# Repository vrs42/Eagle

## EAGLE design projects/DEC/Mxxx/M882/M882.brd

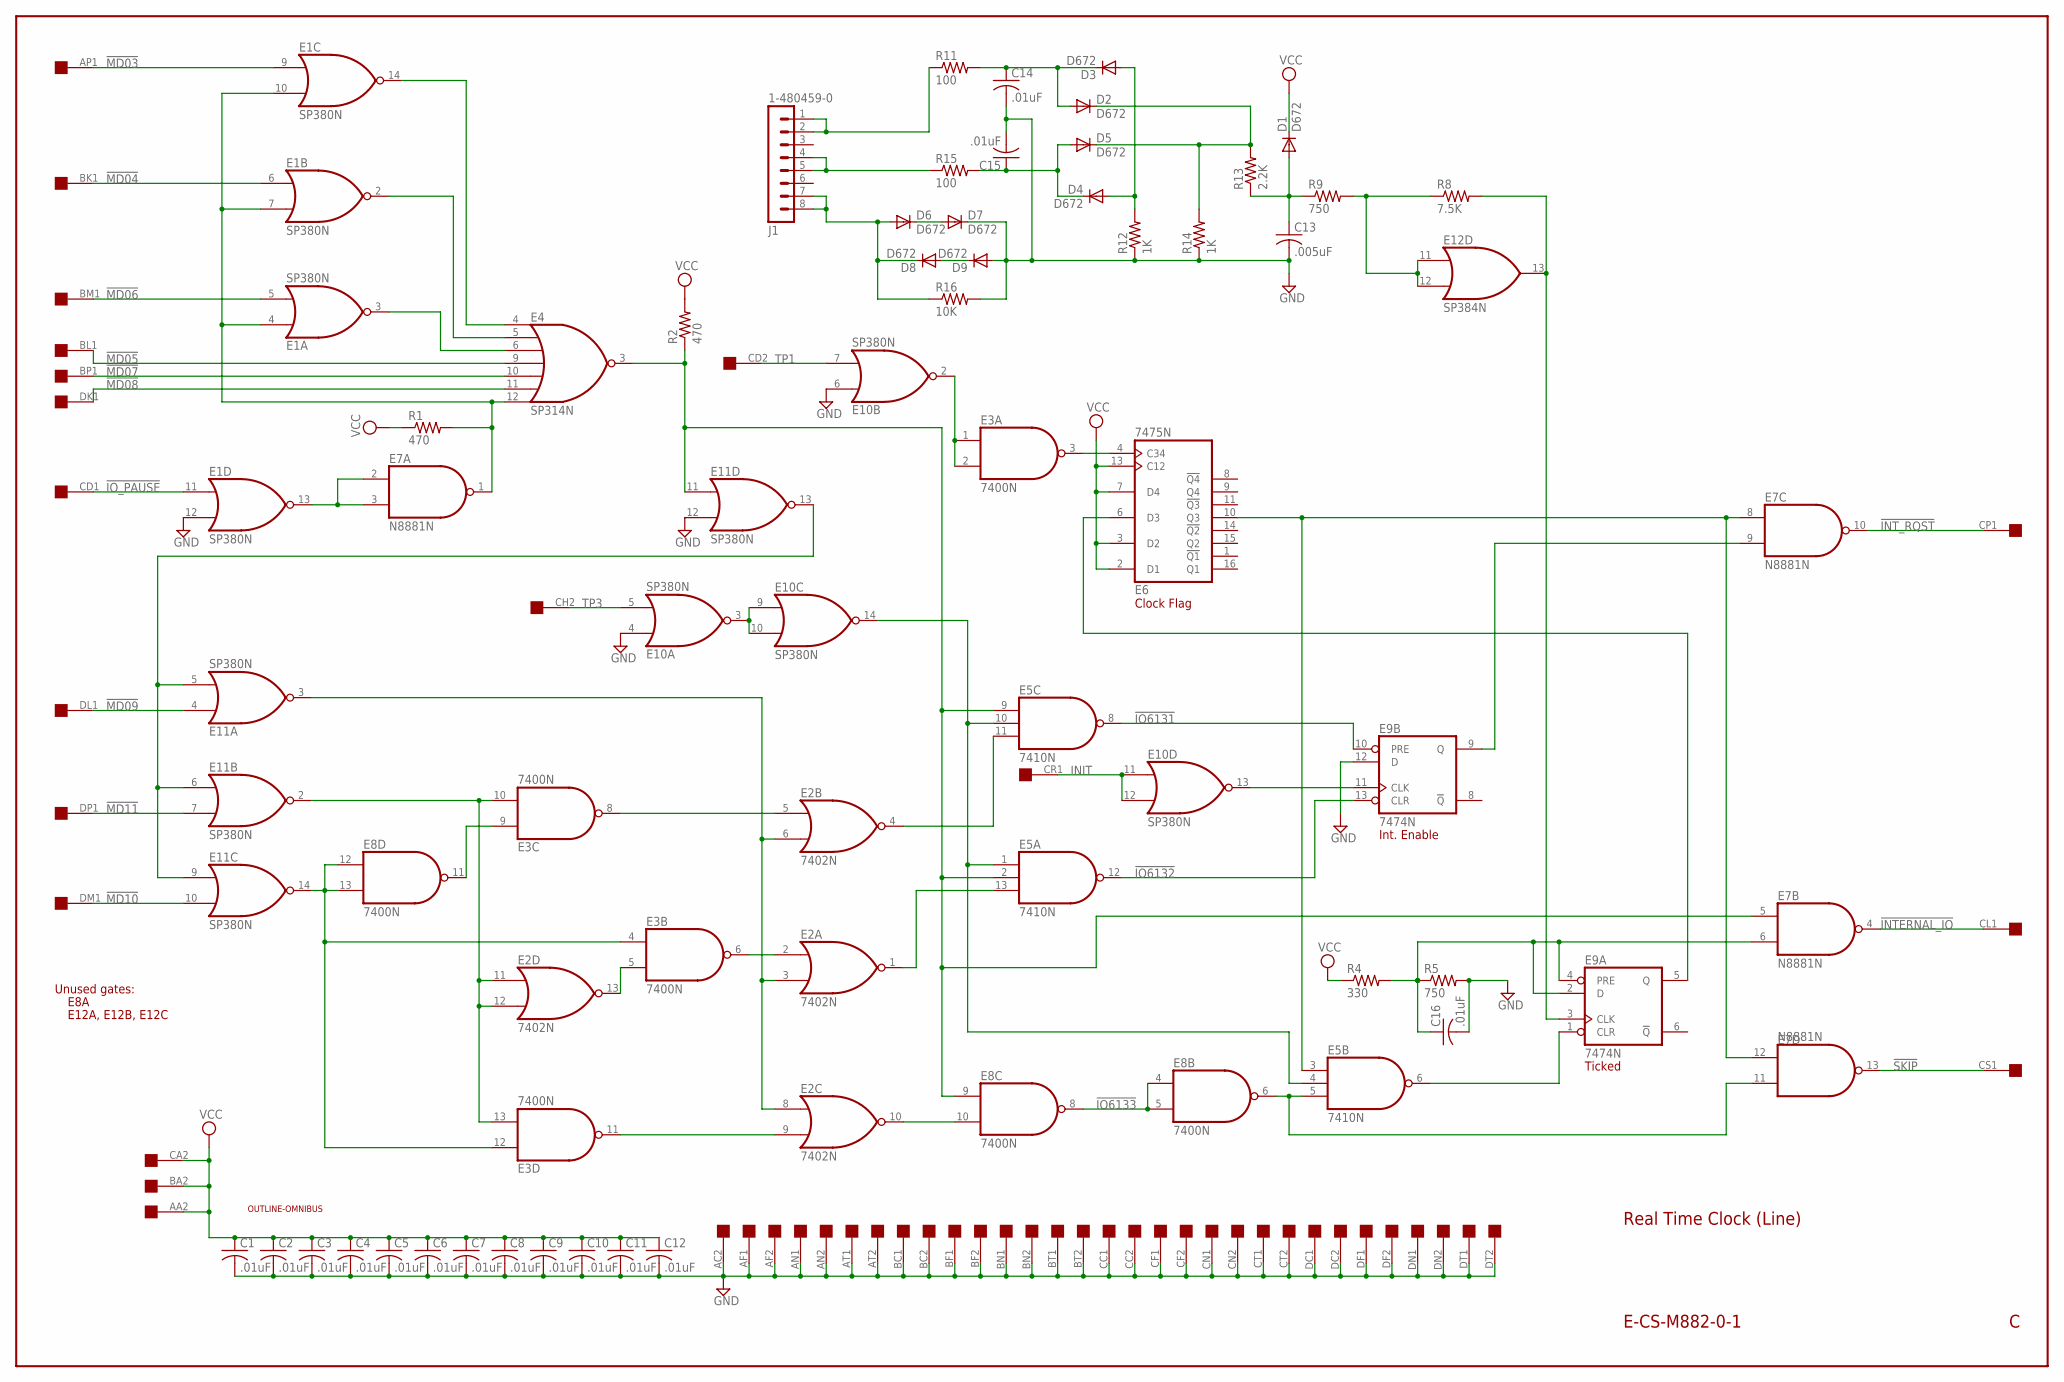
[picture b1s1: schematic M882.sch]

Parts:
C1, C2, C3, C4, C5, C6, C7, C8, C9, C10, C11, C12, C14, C15, C16: .01uF; C050-025X075
C13: .005uF; C050-025X075
D1, D2, D3, D4, D5, D6, D7, D8, D9: D672; DO35-10
E1, E10, E11: SP380N; DIL14
E2: 7402N; DIL14
E3, E8: 7400N; DIL14
E4: SP314N; DIL14
E5: 7410N; DIL14
E6: 7475N; DIL16
E7: N8881N; DIL14
E9: 7474N; DIL14
E12: SP384N; DIL14
EDGE: QUAD; EDGE-CON8
J1: 1-480459-0
R1, R2: 470; 0207/10
R4: 330; 0207/10
R5, R9: 750; 0207/10
R8: 7.5K; 0207/10
R11, R15: 100; 0207/10
R12, R14: 1K; 0207/10
R13: 2.2K; 0207/10
R16: 10K; 0207/10
U$1: OUTLINE-OMNIBUS; OMNIBUS

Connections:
!BIOPAUSE: E1.4 (I0), E1.7 (I1), E1.10 (I1), E4.12 (I6), E7.1 (O), R1.2
!DO_CLSK: E5.6 (O), E9.1 (CLR)
!INIT: E9.11 (CLK), E10.13 (O)
!INTERNAL_IO: E7.4 (O), EDGE.CL1
!INT_RQST: E7.10 (O), EDGE.CP1
!IO6131: E5.8 (O), E9.10 (PRE)
!IO6132: E5.12 (O), E9.13 (CLR)
!IO6133: E8.4 (I0), E8.5 (I1), E8.8 (O)
!IO_PAUSE: E1.11 (I0), EDGE.CD1
!MAYBECLDI: E2.2 (I0), E3.6 (O)
!MAYBE_CLEI: E2.5 (I0), E3.8 (O)
!MAYBE_CLSK: E2.9 (I1), E3.11 (O)
!MD03: E1.9 (I0), EDGE.AP1
!MD04: E1.6 (I0), EDGE.BK1
!MD05: E4.9 (I3), EDGE.BL1
!MD06: E1.5 (I1), EDGE.BM1
!MD07: E4.10 (I4), EDGE.BP1
!MD08: E4.11 (I5), EDGE.DK1
!MD09: E11.4 (I0), EDGE.DL1
!MD10: E11.10 (I1), EDGE.DM1
!MD11: E11.7 (I1), EDGE.DP1
!MYIOT: E11.5 (I1), E11.6 (I0), E11.9 (I0), E11.13 (O)
!MYMD10: E3.9 (I0), E8.11 (O)
!MYMD11: E2.13 (O), E3.5 (I1)
!SKIP: E7.13 (O), EDGE.CS1
!TP1: E3.1 (I0), E3.2 (I1), E10.2 (O)
!TP3: E10.3 (O), E10.9 (I0), E10.10 (I1)
+3V3: C16.1, E7.6 (I1), E9.2 (D), E9.4 (PRE), R4.2, R5.1
BOSCIN: E9.3 (CLK), E12.13 (O), R8.2
BTP1: E3.3 (O), E6.4 (C34)
BTP3: E5.1 (I0), E5.4 (I1), E5.10 (I1), E10.14 (O)
CK_FLAG: E5.3 (I0), E6.10 (Q3), E7.8 (I0), E7.12 (I1)
CLDI: E2.1 (O), E5.13 (I2)
CLIE: E2.4 (O), E5.11 (I2)
CLSK: E2.10 (O), E8.10 (I1)
GND: C1.2, C2.2, C3.2, C4.2, C5.2, C6.2, C7.2, C8.2, C9.2, C10.2, C11.2, C12.2, C13.2, C14.2, C15.2, C16.2, D7.C, D9.A, E1.1 (GND), E1.12 (I1), E2.7 (GND), E3.7 (GND), E4.1 (GND), E5.7 (GND), E6.12 (GND), E7.7 (GND), E8.7 (GND), E9.7 (GND), E9.12 (D), E10.1 (GND), E10.4 (I0), E10.6 (I0), E11.1 (GND), E11.12 (I1), E12.1 (GND), EDGE.AC2, EDGE.AF1, EDGE.AF2, EDGE.AN1, EDGE.AN2, EDGE.AT1, EDGE.AT2, EDGE.BC1, EDGE.BC2, EDGE.BF1, EDGE.BF2, EDGE.BN1, EDGE.BN2, EDGE.BT1, EDGE.BT2, EDGE.CC1, EDGE.CC2, EDGE.CF1, EDGE.CF2, EDGE.CN1, EDGE.CN2, EDGE.CT1, EDGE.CT2, EDGE.DC1, EDGE.DC2, EDGE.DF1, EDGE.DF2, EDGE.DN1, EDGE.DN2, EDGE.DT1, EDGE.DT2, R5.2, R12.1, R14.1, R16.2
INIT: E10.11 (I0), E10.12 (I1), EDGE.CR1
IO6133: E5.5 (I2), E7.11 (I0), E8.6 (O)
IOPMD03: E1.14 (O), E4.4 (I0)
IOPMD04: E1.2 (O), E4.5 (I1)
IOPMD06: E1.3 (O), E4.6 (I2)
IO_PAUSE: E1.13 (O), E7.2 (I0), E7.3 (I1)
IRQ_ENABLE: E7.9 (I1), E9.9 (Q)
MYIOT: E4.3 (O), E5.2 (I1), E5.9 (I0), E7.5 (I0), E8.9 (I0), E11.11 (I0), R2.1
MYMD09: E2.3 (I1), E2.6 (I1), E2.8 (I0), E11.3 (O)
MYMD10: E3.4 (I0), E3.12 (I0), E8.12 (I0), E8.13 (I1), E11.14 (O)
MYMD11: E2.11 (I0), E2.12 (I1), E3.10 (I1), E3.13 (I1), E11.2 (O)
unnamed: J1.1, J1.2, R11.1
unnamed: J1.4, J1.5, R15.1
unnamed: D6.A, D8.C, J1.7, J1.8, R16.1
unnamed: D6.C, D7.A
unnamed: D8.A, D9.C
unnamed: D2.C, D5.C, R13.2, R14.2
unnamed: C14.1, D2.A, D3.C, R11.2
unnamed: D3.A, D4.A, R12.2
unnamed: C13.1, D1.A, R9.1, R13.1
unnamed: C15.1, D4.C, D5.A, R15.2
OSCIN: E12.11 (I0), E12.12 (I1), R8.1, R9.2
TICKED: E6.6 (D3), E9.5 (Q)
TP1: E10.7 (I1), EDGE.CD2
TP3: E10.5 (I1), EDGE.CH2
VCC: C1.1, C2.1, C3.1, C4.1, C5.1, C6.1, C7.1, C8.1, C9.1, C10.1, C11.1, C12.1, D1.C, E1.8 (VCC), E2.14 (VCC), E3.14 (VCC), E4.8 (VCC), E5.14 (VCC), E6.2 (D1), E6.3 (D2), E6.5 (VCC), E6.7 (D4), E6.13 (C12), E7.14 (VCC), E8.14 (VCC), E9.14 (VCC), E10.8 (VCC), E11.8 (VCC), E12.8 (VCC), EDGE.AA2, EDGE.BA2, EDGE.CA2, R1.1, R2.2, R4.1

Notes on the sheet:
Unused gates:
E12A, E12B, E12C
E8A
E-CS-M882-0-1
Real Time Clock (Line)
Int. Enable
Ticked
Clock Flag

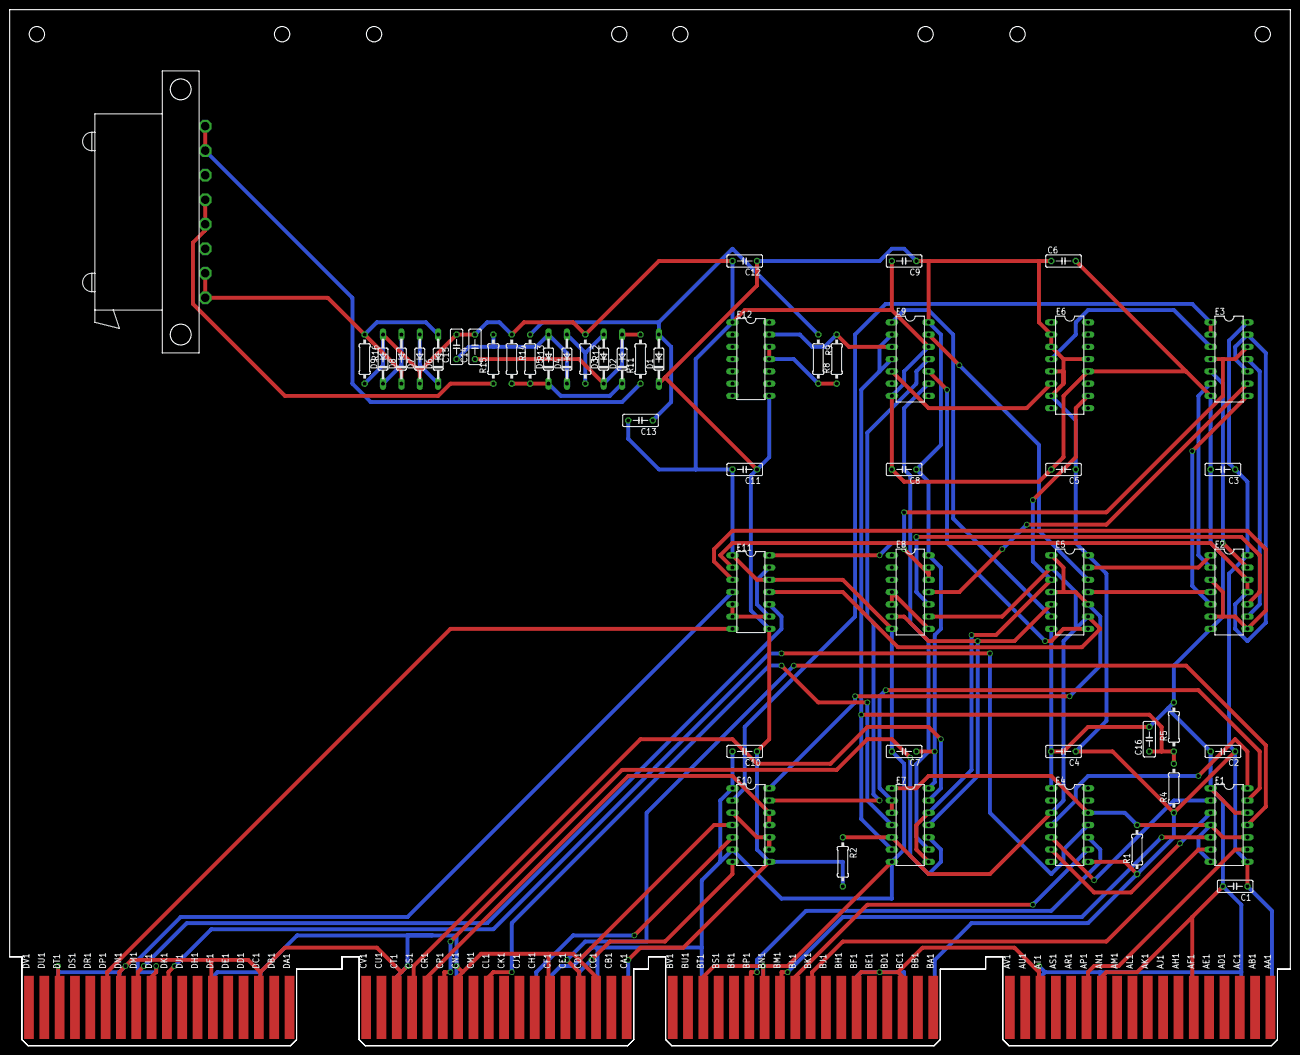
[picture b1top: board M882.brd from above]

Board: 2 copper layers, 265.3 x 214.6 mm, 52 parts (0 on the bottom side), 62 nets.

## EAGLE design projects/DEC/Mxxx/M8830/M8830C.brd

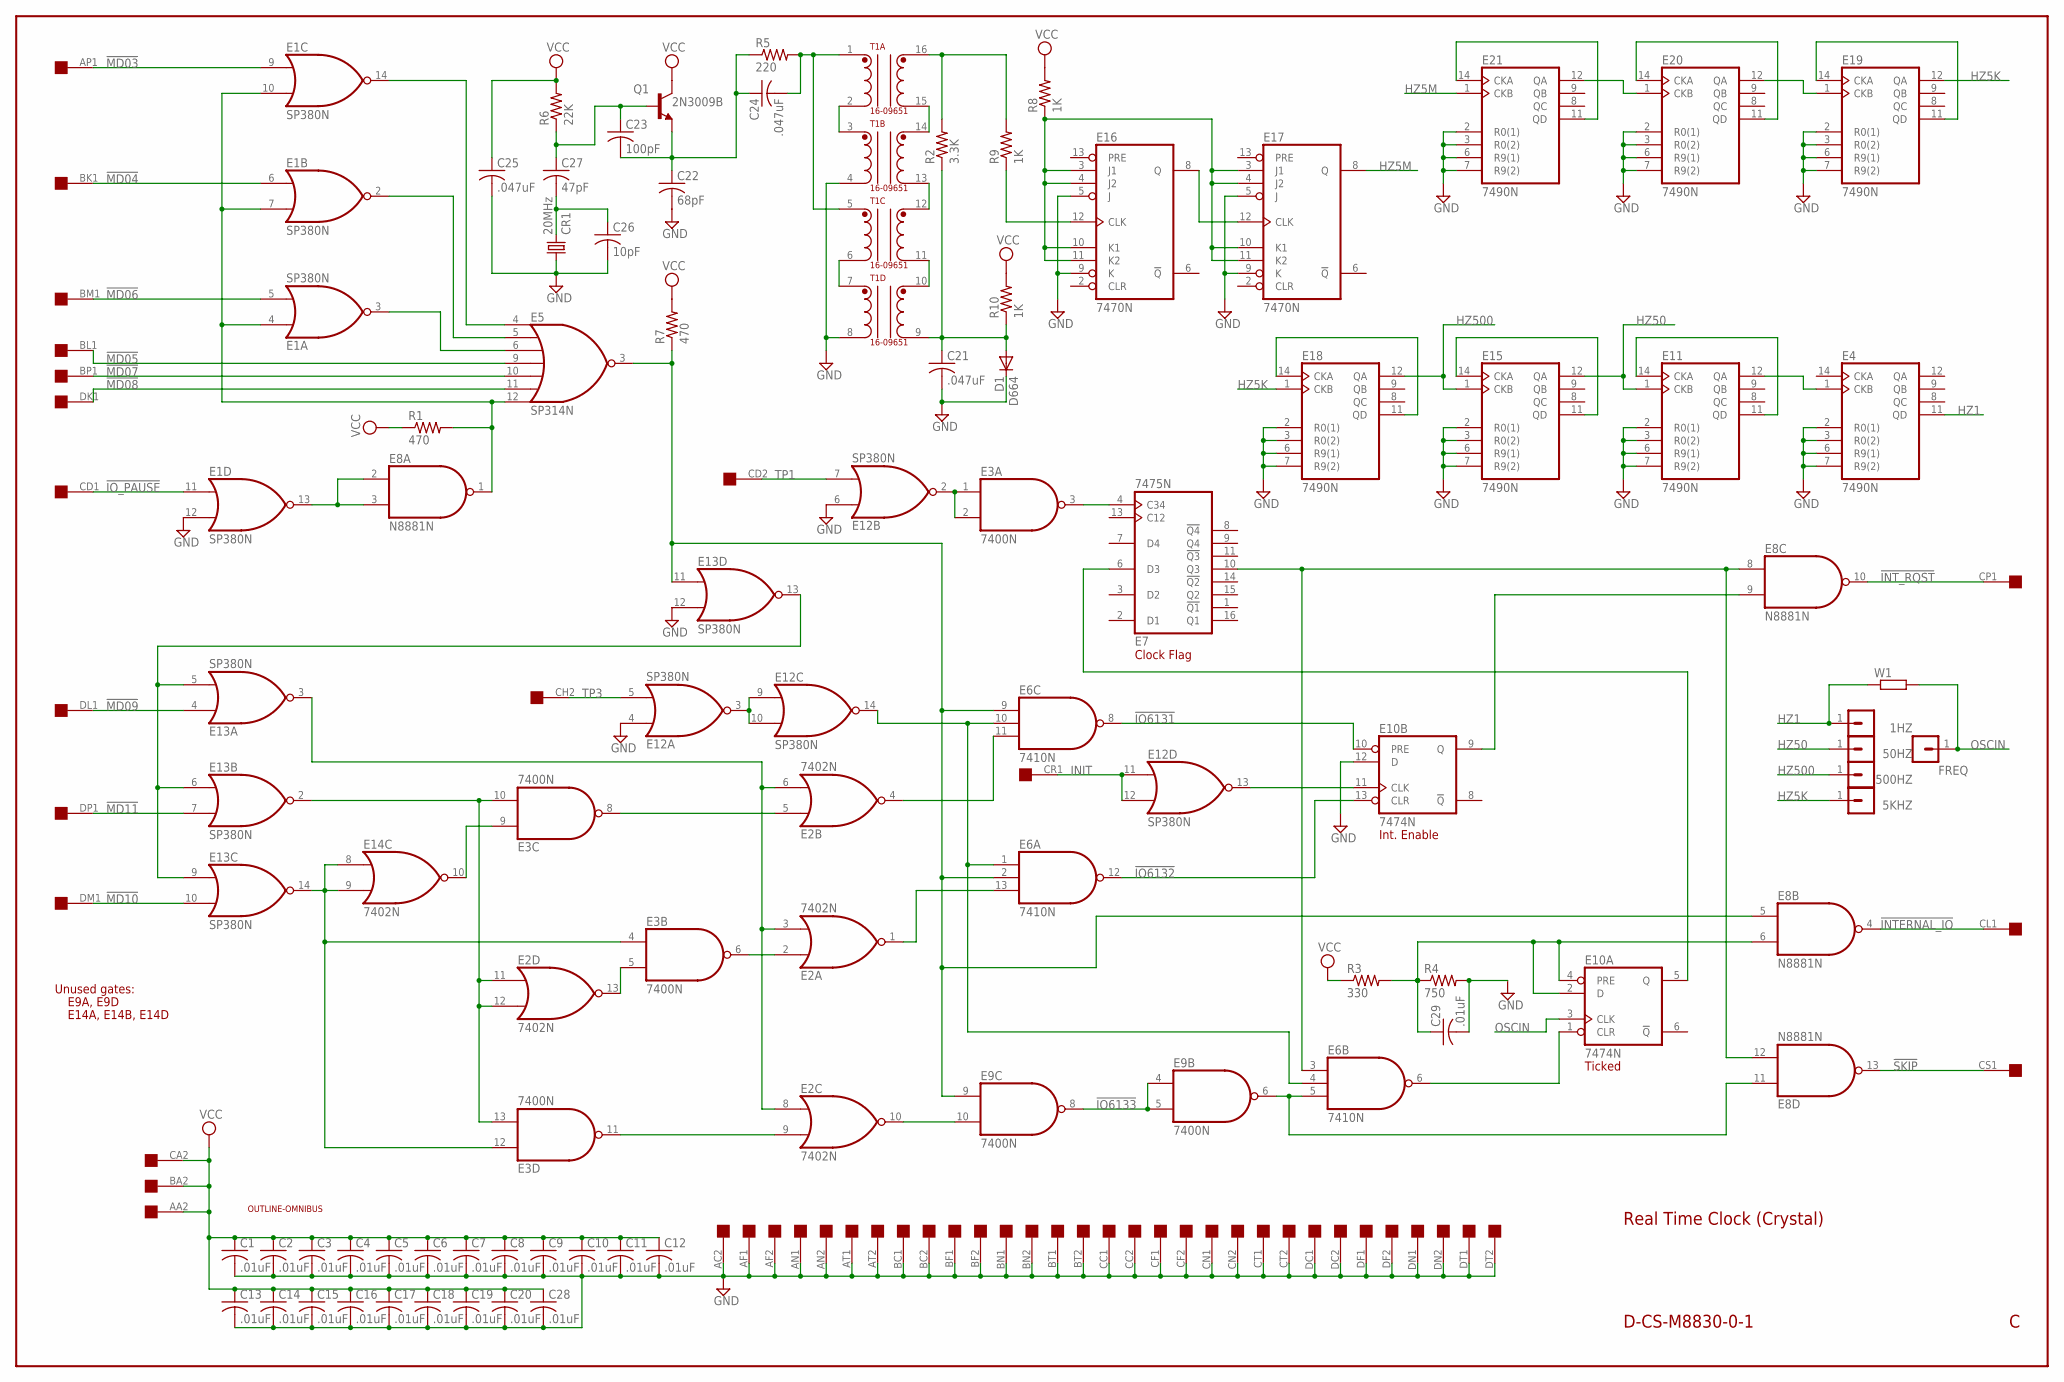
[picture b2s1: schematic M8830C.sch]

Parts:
1HZ, 5KHZ, 50HZ, 500HZ: MA01-1
C1, C2, C3, C4, C5, C6, C7, C8, C9, C10, C11, C12, C13, C14, C15, C16, C17, C18, C19, C20, C28, C29: .01uF; C050-025X075
C21, C24, C25: .047uF; C050-025X075
C22: 68pF; C050-025X075
C23: 100pF; C050-025X075
C26: 10pF; C050-025X075
C27: 47pF; C050-025X075
CR1: 20MHz; HC49TL-H
D1: D664; DO35-10
E1, E12, E13: SP380N; DIL14
E2, E14: 7402N; DIL14
E3, E9: 7400N; DIL14
E4, E11, E15, E18, E19, E20, E21: 7490N; DIL14
E5: SP314N; DIL14
E6: 7410N; DIL14
E7: 7475N; DIL16
E8: N8881N; DIL14
E10: 7474N; DIL14
E16, E17: 7470N; DIL14
EDGE: EDGE-CON8
FREQ: MA01-1
Q1: 2N3009B; TO5
R1, R7: 470; 0207/10
R2: 3.3K; 0207/10
R3: 330; 0207/10
R4: 750; 0207/10
R5: 220; 0207/10
R6: 22K; 0207/10
R8, R9, R10: 1K; 0207/10
T1: 16-09651; DIL16
U$1: OUTLINE-OMNIBUS; OMNIBUS
W1: 0207/10

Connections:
!BIOPAUSE: E1.4 (I0), E1.7 (I1), E1.10 (I1), E5.12 (I6), E8.1 (O), R1.2
!DO_CLSK: E6.6 (O), E10.1 (CLR)
!INIT: E10.11 (CLK), E12.13 (O)
!INTERNAL_IO: E8.4 (O), EDGE.CL1
!INT_RQST: E8.10 (O), EDGE.CP1
!IO6131: E6.8 (O), E10.10 (PRE)
!IO6132: E6.12 (O), E10.13 (CLR)
!IO6133: E9.4 (I0), E9.5 (I1), E9.8 (O)
!IO_PAUSE: E1.11 (I0), EDGE.CD1
!MAYBECLDI: E2.2 (I0), E3.6 (O)
!MAYBE_CLEI: E2.5 (I0), E3.8 (O)
!MAYBE_CLSK: E2.9 (I1), E3.11 (O)
!MD03: E1.9 (I0), EDGE.AP1
!MD04: E1.6 (I0), EDGE.BK1
!MD05: E5.9 (I3), EDGE.BL1
!MD06: E1.5 (I1), EDGE.BM1
!MD07: E5.10 (I4), EDGE.BP1
!MD08: E5.11 (I5), EDGE.DK1
!MD09: E13.4 (I0), EDGE.DL1
!MD10: E13.10 (I1), EDGE.DM1
!MD11: E13.7 (I1), EDGE.DP1
!MYIOT: E13.5 (I1), E13.6 (I0), E13.9 (I0), E13.13 (O)
!MYMD10: E3.9 (I0), E14.10 (O)
!MYMD11: E2.13 (O), E3.5 (I1)
!SKIP: E8.13 (O), EDGE.CS1
!TP1: E3.1 (I0), E3.2 (I1), E12.2 (O)
!TP3: E12.3 (O), E12.9 (I0), E12.10 (I1)
+3V3: C29.1, E8.6 (I1), E10.2 (D), E10.4 (PRE), R3.2, R4.1
BTP1: E3.3 (O), E7.4 (C34)
BTP3: E6.1 (I0), E6.4 (I1), E6.10 (I1), E12.14 (O)
CK_FLAG: E6.3 (I0), E7.10 (Q3), E8.8 (I0), E8.12 (I1)
CLDI: E2.1 (O), E6.13 (I2)
CLIE: E2.4 (O), E6.11 (I2)
CLSK: E2.10 (O), E9.10 (I1)
GND: C1.2, C2.2, C3.2, C4.2, C5.2, C6.2, C7.2, C8.2, C9.2, C10.2, C11.2, C12.2, C13.2, C14.2, C15.2, C16.2, C17.2, C18.2, C19.2, C20.2, C21.2, C22.2, C25.2, C26.2, C28.2, C29.2, CR1.1, D1.C, E1.1 (GND), E1.12 (I1), E2.7 (GND), E3.7 (GND), E4.2 (R0(1)), E4.3 (R0(2)), E4.6 (R9(1)), E4.7 (R9(2)), E4.10 (GND), E5.1 (GND), E6.7 (GND), E7.12 (GND), E8.7 (GND), E9.7 (GND), E10.7 (GND), E10.12 (D), E11.2 (R0(1)), E11.3 (R0(2)), E11.6 (R9(1)), E11.7 (R9(2)), E11.10 (GND), E12.1 (GND), E12.4 (I0), E12.6 (I0), E13.1 (GND), E13.12 (I1), E14.7 (GND), E15.2 (R0(1)), E15.3 (R0(2)), E15.6 (R9(1)), E15.7 (R9(2)), E15.10 (GND), E16.5 (J), E16.7 (GND), E16.9 (K), E17.5 (J), E17.7 (GND), E17.9 (K), E18.2 (R0(1)), E18.3 (R0(2)), E18.6 (R9(1)), E18.7 (R9(2)), E18.10 (GND), E19.2 (R0(1)), E19.3 (R0(2)), E19.6 (R9(1)), E19.7 (R9(2)), E19.10 (GND), E20.2 (R0(1)), E20.3 (R0(2)), E20.6 (R9(1)), E20.7 (R9(2)), E20.10 (GND), E21.2 (R0(1)), E21.3 (R0(2)), E21.6 (R9(1)), E21.7 (R9(2)), E21.10 (GND), EDGE.AC2, EDGE.AF1, EDGE.AF2, EDGE.AN1, EDGE.AN2, EDGE.AT1, EDGE.AT2, EDGE.BC1, EDGE.BC2, EDGE.BF1, EDGE.BF2, EDGE.BN1, EDGE.BN2, EDGE.BT1, EDGE.BT2, EDGE.CC1, EDGE.CC2, EDGE.CF1, EDGE.CF2, EDGE.CN1, EDGE.CN2, EDGE.CT1, EDGE.CT2, EDGE.DC1, EDGE.DC2, EDGE.DF1, EDGE.DF2, EDGE.DN1, EDGE.DN2, EDGE.DT1, EDGE.DT2, R4.2, T1.4, T1.8
HZ1: 1HZ.1, E4.11 (QD), W1.1
HZ5: E4.1 (CKB), E11.12 (QA)
HZ5K: 5KHZ.1, E18.1 (CKB), E19.12 (QA)
HZ5M: E17.8 (Q), E21.1 (CKB)
HZ10M: E16.8 (Q), E17.12 (CLK)
HZ50: 50HZ.1, E11.1 (CKB), E15.12 (QA)
HZ50K: E19.1 (CKB), E20.12 (QA)
HZ500: 500HZ.1, E15.1 (CKB), E18.12 (QA)
HZ500K: E20.1 (CKB), E21.12 (QA)
INIT: E12.11 (I0), E12.12 (I1), EDGE.CR1
IO6133: E6.5 (I2), E8.11 (I0), E9.6 (O)
IOPMD03: E1.14 (O), E5.4 (I0)
IOPMD04: E1.2 (O), E5.5 (I1)
IOPMD06: E1.3 (O), E5.6 (I2)
IO_PAUSE: E1.13 (O), E8.2 (I0), E8.3 (I1)
IRQ_ENABLE: E8.9 (I1), E10.9 (Q)
MYIOT: E5.3 (O), E6.2 (I1), E6.9 (I0), E8.5 (I0), E9.9 (I0), E13.11 (I0), R7.1
MYMD09: E2.3 (I1), E2.6 (I1), E2.8 (I0), E13.3 (O)
MYMD10: E3.4 (I0), E3.12 (I0), E13.14 (O), E14.8 (I0), E14.9 (I1)
MYMD11: E2.11 (I0), E2.12 (I1), E3.10 (I1), E3.13 (I1), E13.2 (O)
unnamed: T1.2, T1.3
unnamed: T1.14, T1.15
unnamed: E11.11 (QD), E11.14 (CKA)
unnamed: E15.11 (QD), E15.14 (CKA)
unnamed: E18.11 (QD), E18.14 (CKA)
unnamed: E19.11 (QD), E19.14 (CKA)
unnamed: E20.11 (QD), E20.14 (CKA)
unnamed: E21.11 (QD), E21.14 (CKA)
unnamed: E16.3 (J1), E16.4 (J2), E16.10 (K1), E16.11 (K2), E17.3 (J1), E17.4 (J2), E17.10 (K1), E17.11 (K2), R8.1
unnamed: T1.12, T1.13
unnamed: R2.2, R9.2, T1.16
unnamed: T1.6, T1.7
unnamed: T1.10, T1.11
unnamed: C21.1, D1.A, R2.1, R10.1, T1.9
unnamed: E16.12 (CLK), R9.1
unnamed: C23.1, C27.1, Q1.2 (B), R6.1
unnamed: C26.1, C27.2, CR1.2
unnamed: C22.1, C23.2, C24.1, Q1.1 (E), R5.1
unnamed: C24.2, R5.2, T1.1, T1.5
OSCIN: E10.3 (CLK), FREQ.1, W1.2
TICKED: E7.6 (D3), E10.5 (Q)
TP1: E12.7 (I1), EDGE.CD2
TP3: E12.5 (I1), EDGE.CH2
VCC: C1.1, C2.1, C3.1, C4.1, C5.1, C6.1, C7.1, C8.1, C9.1, C10.1, C11.1, C12.1, C13.1, C14.1, C15.1, C16.1, C17.1, C18.1, C19.1, C20.1, C25.1, C28.1, E1.8 (VCC), E2.14 (VCC), E3.14 (VCC), E4.5 (VCC), E5.8 (VCC), E6.14 (VCC), E7.5 (VCC), E8.14 (VCC), E9.14 (VCC), E10.14 (VCC), E11.5 (VCC), E12.8 (VCC), E13.8 (VCC), E14.14 (VCC), E15.5 (VCC), E16.14 (VCC), E17.14 (VCC), E18.5 (VCC), E19.5 (VCC), E20.5 (VCC), E21.5 (VCC), EDGE.AA2, EDGE.BA2, EDGE.CA2, Q1.3 (C), R1.1, R3.1, R6.2, R7.2, R8.2, R10.2

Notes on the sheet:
Unused gates:
E14A, E14B, E14D
E9A, E9D
D-CS-M8830-0-1
Real Time Clock (Crystal)
Int. Enable
Ticked
Clock Flag

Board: 2 copper layers, 72 parts (0 on the bottom side), 79 nets, no tracks yet.

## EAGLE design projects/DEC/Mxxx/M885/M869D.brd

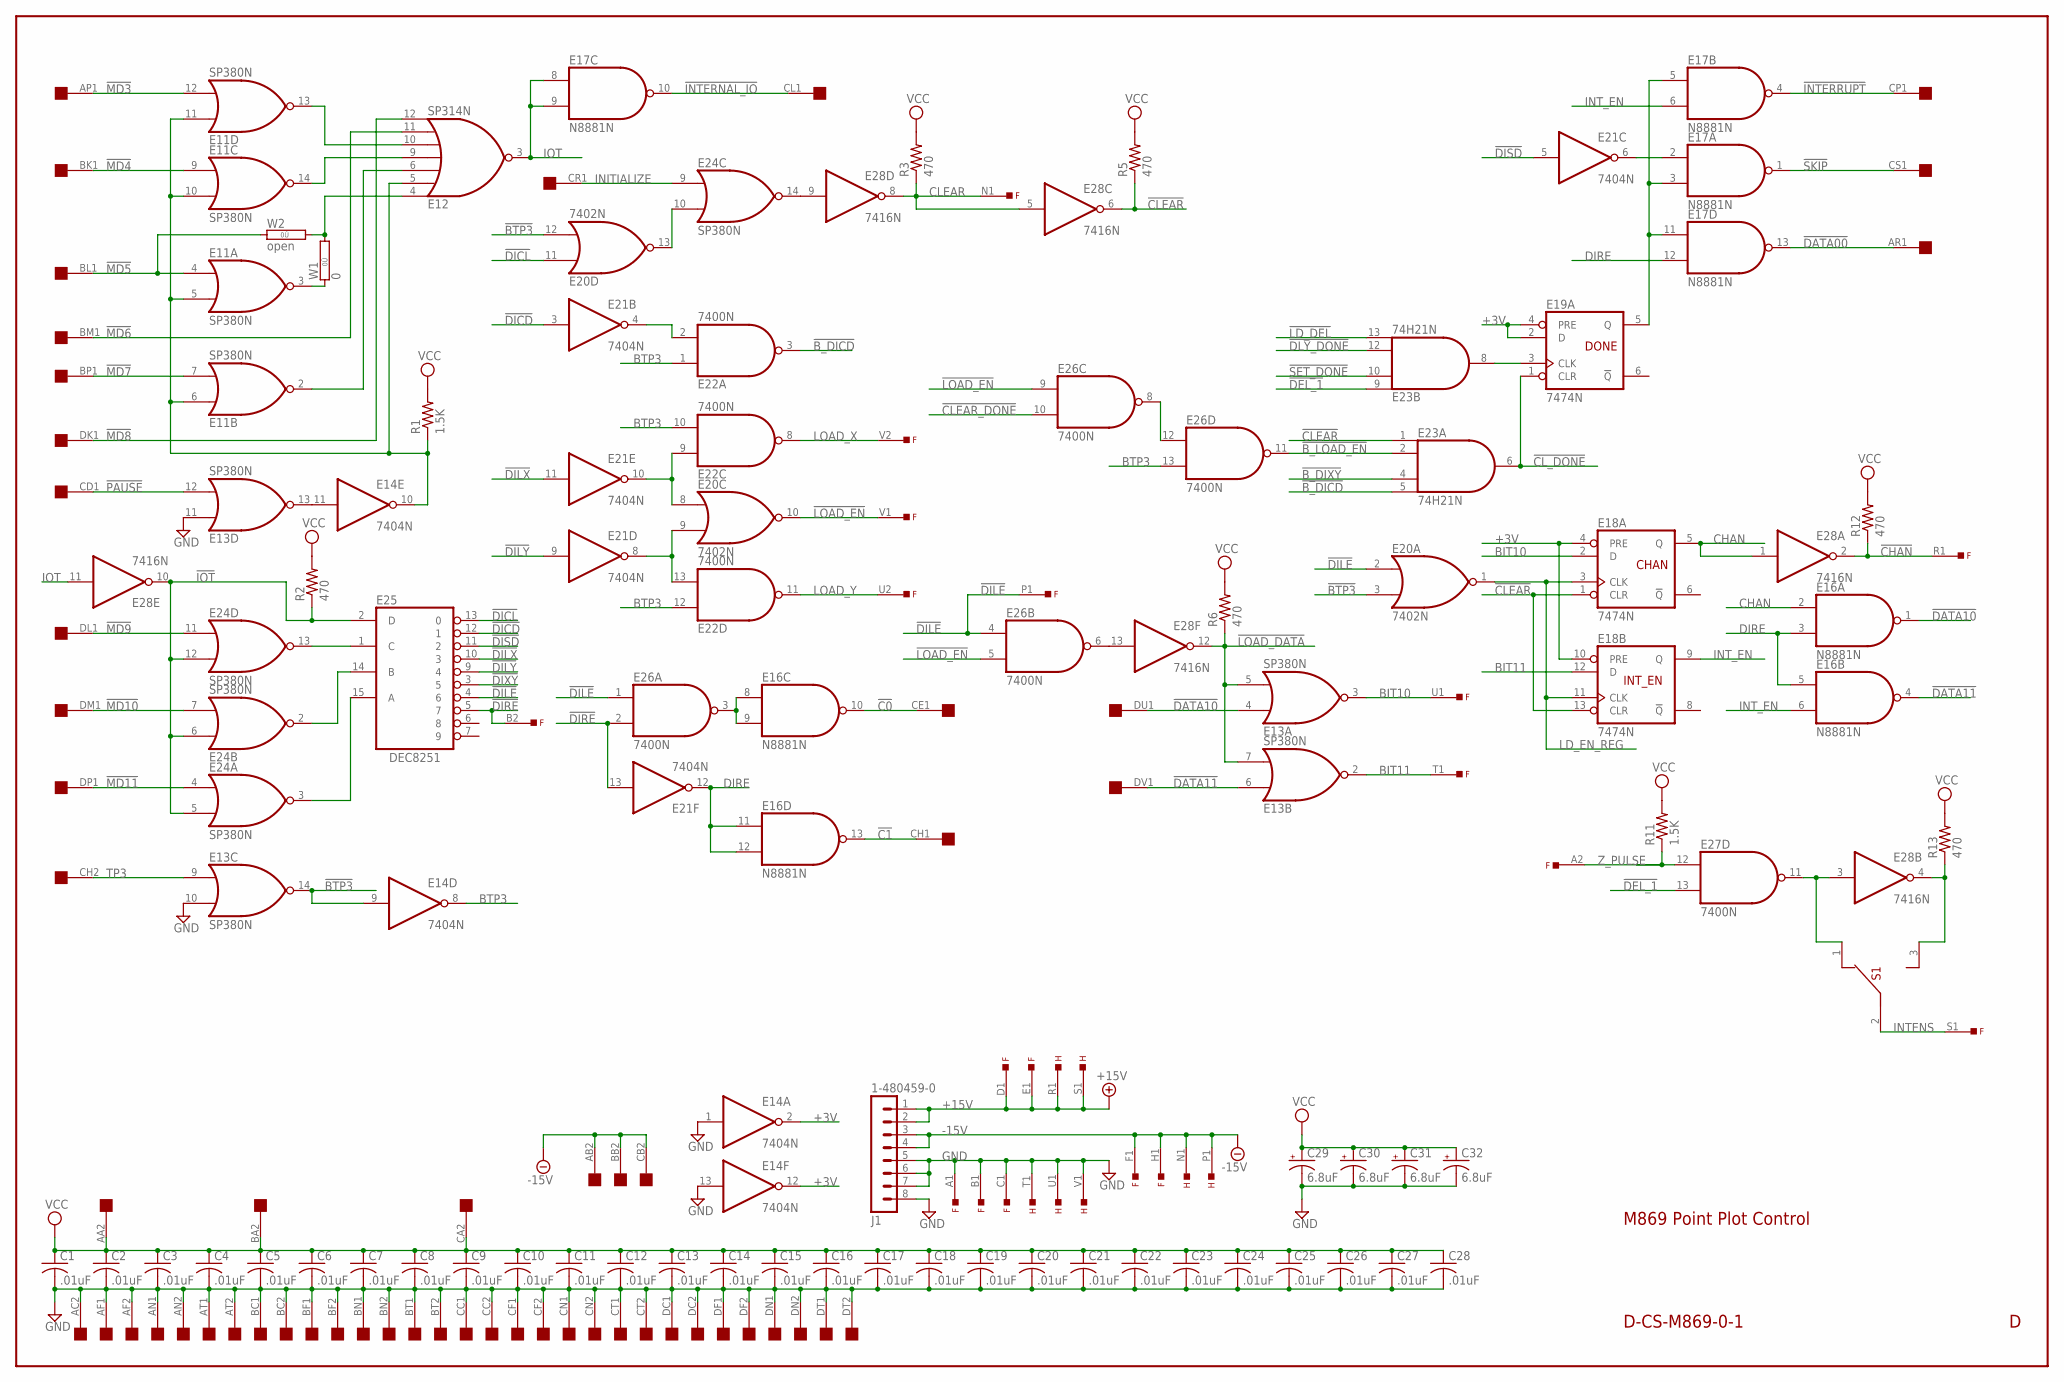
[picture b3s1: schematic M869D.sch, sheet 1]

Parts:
C1, C2, C3, C4, C5, C6, C7, C8, C9, C10, C11, C12, C13, C14, C15, C16, C17, C18, C19, C20, C21, C22, C23, C24, C25, C26, C27, C28: .01uF; C063-025X075
C29, C30, C31, C32: 6.8uF; E12-8
E11, E13, E24: SP380N; DIL14
E12: SP314N; DIL14
E14, E21: 7404N; DIL14
E16, E17: N8881N; DIL14
E18, E19: 7474N; DIL14
E20: 7402N; DIL14
E22, E26, E27: 7400N; DIL14
E23: 74H21N; DIL14
E25: DEC8251; DIL16
E28: 7416N; DIL14
F: EDGE-TOP; EDGE-CON2
H: EDGE-TOP; EDGE-CON2
J1: 1-480459-0
OMNIBUS: QUAD; EDGE-CON8
R1, R11: 1.5K; 0207/10
R2, R3, R5, R6, R12, R13: 470; 0207/10
S1: 12-09698; 23-021
W1: 0; 0R/10
W2: open; 0R/10

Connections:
!BTP3: E13.14 (O), E14.9 (I), E20.3 (I1), E20.12 (I1)
!B_DICD: E22.3 (O), E23.5 (I3)
!B_DIXY: E23.4 (I2); also elsewhere on the board
!B_LOAD_EN: E23.2 (I1), E26.11 (O)
!C0: E16.10 (O), OMNIBUS.CE1
!C1: E16.13 (O), OMNIBUS.CH1
!CHAN: E28.2 (O), F.R1, R12.1
!CLEAR: E18.1 (CLR), E18.13 (CLR), E23.1 (I0), E28.6 (O), R5.1; also elsewhere on the board
!CLEAR_DONE: E26.10 (I1); also elsewhere on the board
!CL_DONE: E19.1 (CLR), E23.6 (O)
!DATA00: E17.13 (O), OMNIBUS.AR1
!DATA10: E13.4 (I0), E16.1 (O), OMNIBUS.DU1
!DATA11: E13.6 (I0), E16.4 (O), OMNIBUS.DV1
!DEL_1: E23.9 (I0), E27.13 (I1); also elsewhere on the board
!DICD: E21.3 (I), E25.12 (1)
!DICL: E20.11 (I0), E25.13 (0)
!DILE: E20.2 (I0), E25.4 (6), E26.1 (I0), E26.4 (I0), F.P1
!DILX: E21.11 (I), E25.10 (3)
!DILY: E21.9 (I), E25.9 (4)
!DIRE: E21.13 (I), E25.5 (7), E26.2 (I1), F.B2
!DISD: E21.5 (I), E25.11 (2)
!DIXY: E25.3 (5); also elsewhere on the board
!DLY_DONE: E23.12 (I2); also elsewhere on the board
!INTERNAL_IO: E17.10 (O), OMNIBUS.CL1
!INTERRUPT: E17.4 (O), OMNIBUS.CP1
!IOT: E24.5 (I1), E24.6 (I0), E24.12 (I1), E25.2 (D), E28.10 (O), R2.1
!LD_DEL: E23.13 (I3); also elsewhere on the board
!LOAD_DATA: E13.5 (I1), E13.7 (I1), E28.12 (O), R6.1; also elsewhere on the board
!LOAD_EN: E20.10 (O), E26.5 (I1), E26.9 (I0), F.V1; also elsewhere on the board
!MD3: E11.12 (I1), OMNIBUS.AP1
!MD4: E11.9 (I0), OMNIBUS.BK1
!MD5: E11.4 (I0), OMNIBUS.BL1, W2.1
!MD6: E12.11 (I5), OMNIBUS.BM1
!MD7: E11.7 (I1), OMNIBUS.BP1
!MD8: E12.12 (I6), OMNIBUS.DK1
!MD9: E24.11 (I0), OMNIBUS.DL1
!MD10: E24.7 (I1), OMNIBUS.DM1
!MD11: E24.4 (I0), OMNIBUS.DP1
!PAUSE: E13.12 (I1), OMNIBUS.CD1
!SET_DONE: E23.10 (I1); also elsewhere on the board
!SKIP: E17.1 (O), OMNIBUS.CS1
+3V: E14.2 (O), E14.12 (O), E18.4 (PRE), E18.10 (PRE), E19.2 (D), E19.4 (PRE); also elsewhere on the board
+15V: F.D1, F.E1, H.R1, H.S1, J1.1, J1.2
-15V: F.F1, F.H1, H.N1, H.P1, J1.3, J1.4, OMNIBUS.AB2, OMNIBUS.BB2, OMNIBUS.CB2
BIT10: E13.3 (O), E18.2 (D), F.U1
BIT11: E13.2 (O), E18.12 (D), F.T1
BTP3: E14.8 (O), E22.1 (I0), E22.10 (I1), E22.12 (I0), E26.13 (I1); also elsewhere on the board
CHAN: E16.2 (I0), E18.5 (Q), E28.1 (I)
CLEAR: E28.5 (I), E28.8 (O), F.N1, R3.1; also elsewhere on the board
DEL_1: E27.11 (O), E28.3 (I), S1.1 (A1)
DEL_1_L: E28.4 (O), R13.1, S1.3 (A3)
DICD: E21.4 (O), E22.2 (I1)
DILX: E20.8 (I0), E21.10 (O), E22.9 (I0)
DILY: E20.9 (I1), E21.8 (O), E22.13 (I1)
DIRE: E16.3 (I1), E16.5 (I0), E16.11 (I0), E16.12 (I1), E17.12 (I1), E21.12 (O); also elsewhere on the board
DISD: E17.2 (I0), E21.6 (O)
GND: C1.2, C2.2, C3.2, C4.2, C5.2, C6.2, C7.2, C8.2, C9.2, C10.2, C11.2, C12.2, C13.2, C14.2, C15.2, C16.2, C17.2, C18.2, C19.2, C20.2, C21.2, C22.2, C23.2, C24.2, C25.2, C26.2, C27.2, C28.2, C29.-, C30.-, C31.-, C32.-, E11.1 (GND), E12.1 (GND), E13.1 (GND), E13.10 (I1), E13.11 (I0), E14.1 (I), E14.7 (GND), E14.13 (I), E16.7 (GND), E17.7 (GND), E18.7 (GND), E19.7 (GND), E20.7 (GND), E21.7 (GND), E22.7 (GND), E23.7 (GND), E24.1 (GND), E25.8 (GND), E26.7 (GND), E27.7 (GND), E28.7 (GND), F.A1, F.B1, F.C1, H.T1, H.U1, H.V1, J1.5, J1.6, J1.7, J1.8, OMNIBUS.AC2, OMNIBUS.AF1, OMNIBUS.AF2, OMNIBUS.AN1, OMNIBUS.AN2, OMNIBUS.AT1, OMNIBUS.AT2, OMNIBUS.BC1, OMNIBUS.BC2, OMNIBUS.BF1, OMNIBUS.BF2, OMNIBUS.BN1, OMNIBUS.BN2, OMNIBUS.BT1, OMNIBUS.BT2, OMNIBUS.CC1, OMNIBUS.CC2, OMNIBUS.CF1, OMNIBUS.CF2, OMNIBUS.CN1, OMNIBUS.CN2, OMNIBUS.CT1, OMNIBUS.CT2, OMNIBUS.DC1, OMNIBUS.DC2, OMNIBUS.DF1, OMNIBUS.DF2, OMNIBUS.DN1, OMNIBUS.DN2, OMNIBUS.DT1, OMNIBUS.DT2; also elsewhere on the board
INITIALIZE: E24.9 (I0), OMNIBUS.CR1
INTENS: F.S1, S1.2 (A2)
INT_EN: E16.6 (I1), E17.6 (I1), E18.9 (Q)
IO3: E11.13 (O), E12.10 (I4)
IO4: E11.14 (O), E12.9 (I3)
IO5: E12.4 (I0), W1.2, W2.2
IO7: E11.2 (O), E12.6 (I2)
IOT: E12.3 (O), E17.8 (I0), E17.9 (I1), E28.11 (I)
LD_EN_REG: E18.3 (CLK), E18.11 (CLK), E20.1 (O); also elsewhere on the board
LOAD_X: E22.8 (O), F.V2
LOAD_Y: E22.11 (O), F.U2
MD5: E11.3 (O), W1.1
unnamed: E17.3 (I1), E17.5 (I0), E17.11 (I0), E19.5 (Q)
unnamed: E26.8 (O), E26.12 (I0)
unnamed: E19.3 (CLK), E23.8 (O)
unnamed: E16.8 (I0), E16.9 (I1), E26.3 (O)
unnamed: E26.6 (O), E28.13 (I)
unnamed: E13.13 (O), E14.11 (I)
unnamed: E24.14 (O), E28.9 (I)
unnamed: E24.3 (O), E25.15 (A)
unnamed: E24.2 (O), E25.14 (B)
unnamed: E24.13 (O), E25.1 (C)
unnamed: E20.13 (O), E24.10 (I1)
PAUSE_L: E11.5 (I1), E11.6 (I0), E11.10 (I1), E11.11 (I0), E12.5 (I1), E14.10 (O), R1.1
TP3: E13.9 (I0), OMNIBUS.CH2
VCC: C1.1, C2.1, C3.1, C4.1, C5.1, C6.1, C7.1, C8.1, C9.1, C10.1, C11.1, C12.1, C13.1, C14.1, C15.1, C16.1, C17.1, C18.1, C19.1, C20.1, C21.1, C22.1, C23.1, C24.1, C25.1, C26.1, C27.1, C28.1, C29.+, C30.+, C31.+, C32.+, E11.8 (VCC), E12.8 (VCC), E13.8 (VCC), E14.14 (VCC), E16.14 (VCC), E17.14 (VCC), E18.14 (VCC), E19.14 (VCC), E20.14 (VCC), E21.14 (VCC), E22.14 (VCC), E23.14 (VCC), E24.8 (VCC), E25.16 (VCC), E26.14 (VCC), E27.14 (VCC), E28.14 (VCC), OMNIBUS.AA2, OMNIBUS.BA2, OMNIBUS.CA2, R1.2, R2.2, R3.2, R5.2, R6.2, R11.2, R12.2, R13.2; also elsewhere on the board
Z_PULSE: E27.12 (I0), F.A2, R11.1

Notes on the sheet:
D-CS-M869-0-1
M869 Point Plot Control
DONE
CHAN
INT_EN
